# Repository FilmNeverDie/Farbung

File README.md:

# Farbung

Färbung means colouring in German, and all these effor are infact a way of colouring, thus Färbung. 
A open source project based on FilmNeverDie's CP800 film processing machine.

Project: CP800 

This project is initialized and managed by FIlmeNeverDie. Here, we introduce a rotating drum film developer. Film developing machines are getting outdated and they have run out of support, so the project aims to introduce a series of products that could replace old equipment that has no support and is hard to get replacement/maintenance services. This project provides the resources available for on-going maintenance and product support for film processing within an open-source community, so that anyone can pick up the role as a supplier and maker. We also welcome users to make their own adaptation since the need for each user might be different and the existing variation may not be ideal for each application. Please see CONTIRBUTION for how you can contribute to an existing project, or branch off to your own variant of the machine.  

## Project structure 
 
The project is separated into sections: hardware, firmware, and software 

Hardware includes a list of parts, the relevant CAD files, schematics, and respective documentation such as part lists (BOM), datasheet, user manual, maintenance manual, production manual, and certificates. 

Firmware includes the codes for programming the microcontroller, and its respective documentation such as change log, license, dependency. 

Software includes any software that enhance any parts of either the machines or film processing such as simulation, check system integrity and firmware auto-update, the processing programs generators, photo scanning and processing software and their respective documentation such as change log, license, dependency. 

Contributors will be expected writing and updating the manuals for their own variation.  

There will be a list of verified models and compatibility table that shows the combination of hardware/firmware/software compatible in the front page of each project.  

## Getting Started 

Installations 

### Firmware: 

Arduino IDE with libraries: 

- USB Host shield Library 2.0  

- DallasTemperautre + OneWire 

Get the newest stable version of source code and upload to the arduino, please check the hardware version of your machine if you purchased from FND, and download the respective firmware. 

### Hardware: 
Mechanical:
Fusion 360 
Electronics:
KiCAD5

### Software:

N/A 

## Getting Involved 

The following are areas where we are currently working on: 

Chemical tanks system: float sensors, heating 

Mechanically stronger developing tank (either stainless steel, or better printing) 

Firmware optimization to use dynamics memory less than 5kbB. 

Optional joystick modules (Arduino joystick shield), and USB/BT controller (see USB Host shield Library for the list) 

Onboard low noise low dropout voltage regulation instead of relying solely on the switching mode convertors with various quality depending on the source (see the BOM in hardware section) 

Areas that could be potential development: 

Miniature solenoid valves and poly manifolds fitting.  

Compatible microcontroller other than Arduino such as beaglebone, Rpi, Psoc, others 

Processing program generators (web base or standalone) 

A bigger and high-resolution screen, also new UI/UX, don't mind if you can fit a few “extra functions” in for bored operators to do while processing 

A computer application that searches for the newest firmware to download from GitHub for any verified hardware 

Any other suggestions 

## Documentation

This repo uses [mkdocs](https://www.mkdocs.org) to host online documentation. `mkdocs.yml` is its configuration file, and `docs/` is the directory containing the documentation pages.

## LICENSE: 

This work is licensed under a Creative Commons Attribution-ShareAlike 4.0 International License, except for source code which is licensed under the 3-Clause BSD License.

see LICENSE.md and LICENSE_CC-BY-SA.md for details

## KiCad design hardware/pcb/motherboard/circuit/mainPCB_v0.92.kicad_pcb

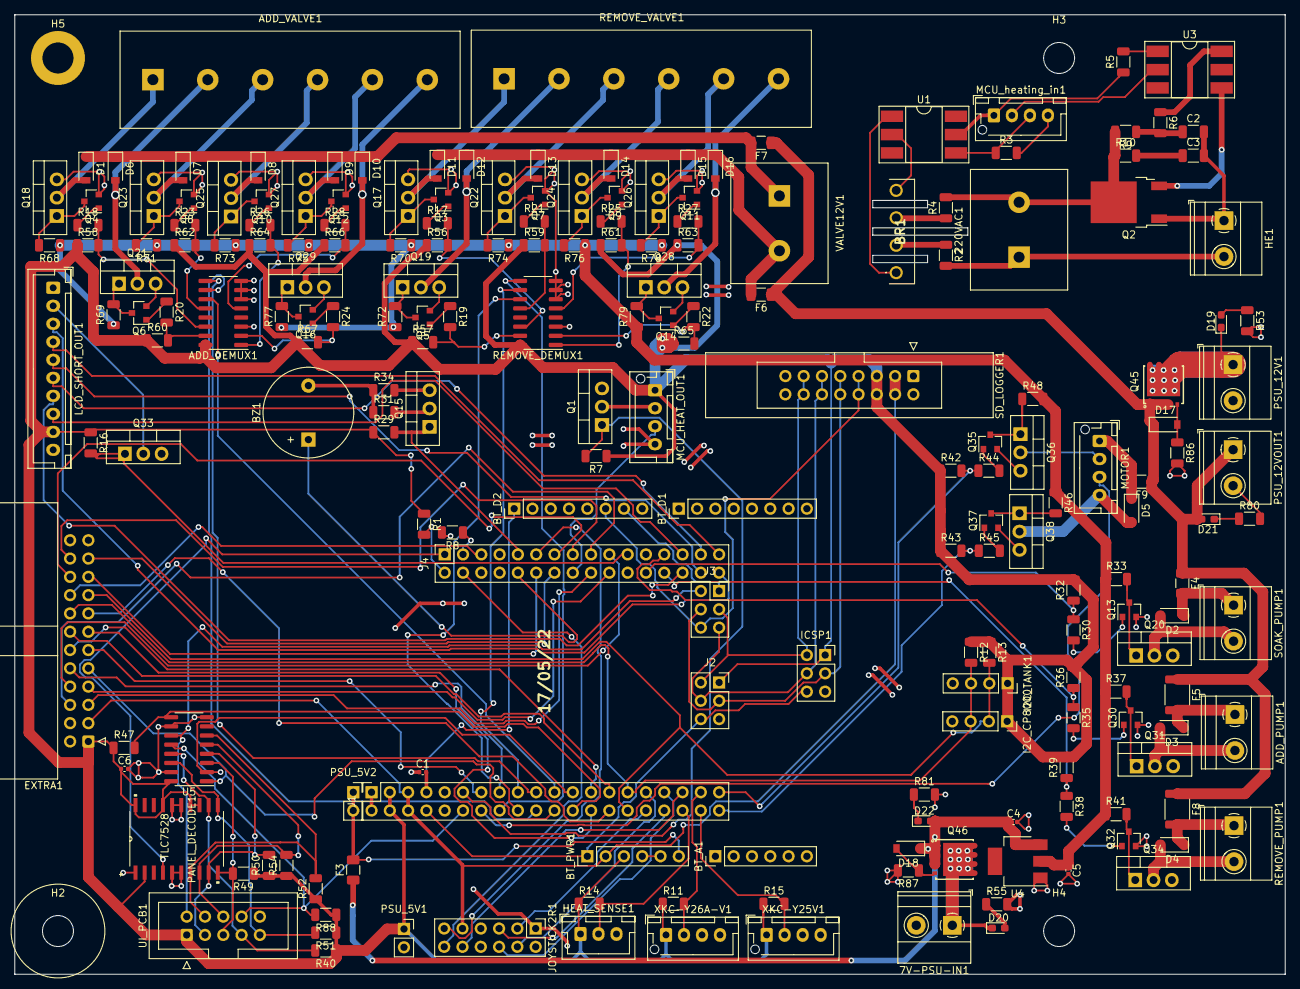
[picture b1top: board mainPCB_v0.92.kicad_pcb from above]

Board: 2 copper layers, 176.4 x 133.2 mm, 207 parts (0 on the bottom side), 174 nets.

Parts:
7V-PSU-IN1: WJ128V-5.0-2P; TerminalBlock_Phoenix_MKDS-1,5-2_1x02_P5.00mm_Horizontal
220VAC1: WJ25C-B-7.62-2P
ADD_DEMUX1: CD4051BM96; SOIC-16_3.9x9.9mm_P1.27mm
ADD_PUMP1: WJ128V-5.0-2P; TerminalBlock_Phoenix_MKDS-1,5-2_1x02_P5.00mm_Horizontal
ADD_VALVE1: WJ25C-B-7.62-6P
BR1: KBP206G
BT_A1: Conn_01x06; PinHeader_1x06_P2.54mm_Vertical
BT_D1, BT_D2: Conn_01x08; PinHeader_1x08_P2.54mm_Vertical
BT_PWR1: Conn_01x06; PinHeader_1x06_P2.54mm_Vertical
BZ1: SFN-1207PA7.6; Buzzer_12.6x7.0P7.5
C1: 100nF-ceramics; C_0402_1005Metric
C2: 47nF-ceramic; C_1206_3216Metric
C3: 10nF-ceramic; C_1206_3216Metric
C4, C5: 1.0uF; C_0402_1005Metric
C6: 0.1uF; C_0402_1005Metric
D1, D2, D3, D4, D5, D6, D7, D8, D9, D10, D11, D12, D13, D14, D15, D16: 1N5819HW-7-F; D_SOD-123
D17: MM1Z12; D_SOD-123
D18: MM1Z7V5; D_SOD-123
D19, D20: RLED; LED_0603_1608Metric_Pad1.05x0.95mm_HandSolder
D21, D22: WLED; LED_0603_1608Metric_Pad1.05x0.95mm_HandSolder
EXTRA1: 321024RG0ABK00A06; IDC-Header_2x12_P2.54mm_Horizontal
F3: BSMD1206-050-13.2V; Fuse_1206_3216Metric
F4: BSMD1206-050-16V; Fuse_1206_3216Metric
F5, F8: BSMD1812-260-13.2V; Fuse_1812_4532Metric
F6, F7: BSMD1206-100-16V; Fuse_1206_3216Metric
F9: BSMD1206-075-16V; Fuse_1206_3216Metric
H2, H3, H4: MountingHole; MountingHole_4.3mm_M4
H5: MountingHole; MountingHole_4.3mm_M4_DIN965_Pad
HE1: WJ128V-5.0-2P; TerminalBlock_Phoenix_MKDS-1,5-2_1x02_P5.00mm_Horizontal
HEAT_SENSE1: JST_XH-A-1x03; JST_XH_B3B-XH-A_1x03_P2.50mm_Vertical
I2C_CP8000, I2C_TANK1: Conn_01x04; PinSocket_1x04_P2.54mm_Vertical
ICSP1: Conn_02x03_Odd_Even; PinSocket_2x03_P2.54mm_Vertical
J1: Conn_02x20_Odd_Even; PinSocket_2x20_P2.54mm_Vertical
J2, J3: Conn_02x03_Odd_Even; PinSocket_2x03_P2.54mm_Vertical
J4: Conn_02x16_Odd_Even; PinSocket_2x16_P2.54mm_Vertical
JOYSTICK2R1: Conn_02x06_Odd_Even; PinHeader_2x06_P2.54mm_Vertical
LCD_SHORT_OUT1: JST_XH-A-1x10; JST_XH_B10B-XH-A_1x10_P2.50mm_Vertical
MCU_HEAT_OUT1: JST_XH-A-1x04; JST_XH_B4B-XH-AM_1x04_P2.50mm_Vertical
MCU_heating_in1: JST_XH-A-1x04; JST_XH_B4B-XH-AM_1x04_P2.50mm_Vertical
MOTOR1: JST_XH-A-1x04; JST_XH_B4B-XH-AM_1x04_P2.50mm_Vertical
PANEL_DECODE1: TLC7528; TLC7528CDW
PSU_5V1, PSU_5V2: Conn_01x02; PinSocket_1x02_P2.54mm_Vertical
PSU_12V1, PSU_12VOUT1: WJ128V-5.0-2P; TerminalBlock_Phoenix_MKDS-1,5-2_1x02_P5.00mm_Horizontal
Q1, Q15, Q33: IRF510PBF; TO-220-3_Vertical
Q2: BT136S-600E; TO-252-2
Q3, Q4, Q5, Q6, Q7, Q8, Q9, Q10, Q11, Q12, Q13, Q14, Q16, Q30, Q32, Q35, Q37: BC847; SOT-23
Q17, Q18, Q19, Q20, Q21, Q22, Q23, Q24, Q25, Q26, Q27, Q28, Q29, Q31, Q34, Q36, Q38: IRF540NPBF; TO-220-3_Vertical
Q45, Q46: AON6411; ALOM_DFN5X6_8L_EP1_P
R1, R7, R8, R11, R12, R13, R15, R16, R29, R30, R32, R35, R36, R38, R39, R40, R42, R43, R44, R45, R47, R49, R50, R51, R52, R54, R56, R57, R58, R59, R60, R61, R62, R63, R64, R65, R66, R67, R86, R87, R88: 10k-0.25W; R_1206_3216Metric
R2, R4: 47k-0.25W; R_1206_3216Metric
R3, R17, R18, R19, R20, R21, R22, R23, R24, R25, R26, R27, R28, R34: 1k-0.25W; R_1206_3216Metric
R5, R68, R69, R70, R71, R72, R73, R74, R75, R76, R77, R78, R79: 150-0.25W; R_1206_3216Metric
R6: 360-0.25W; R_1206_3216Metric
R9: 470-0.25W; R_1206_3216Metric
R10: 68-0.25W; R_1206_3216Metric
R14, R53, R55, R80, R81: 4.7k-0.25W; R_1206_3216Metric
R31: 220-0.25W; R_1206_3216Metric
R33, R37, R41, R46, R48: 200-0.25W; R_1206_3216Metric
REMOVE_DEMUX1: CD4051BM96; SOIC-16_3.9x9.9mm_P1.27mm
REMOVE_PUMP1: WJ128V-5.0-2P; TerminalBlock_Phoenix_MKDS-1,5-2_1x02_P5.00mm_Horizontal
REMOVE_VALVE1: WJ25C-B-7.62-6P
SD_LOGGER1: 321016SG0ABK00A01; IDC-Header_2x08_P2.54mm_Latch_Vertical
SOAK_PUMP1: WJ128V-5.0-2P; TerminalBlock_Phoenix_MKDS-1,5-2_1x02_P5.00mm_Horizontal
U1: 4N35SM; DIP-6_W8.89mm_SMDSocket_LongPads
U3: MOC3020S-TA1; DIP-6_W8.89mm_SMDSocket_LongPads
U4: AZ1117-5.0; SOT-223
U5: SN74HC165; SOIC-16_3.9x9.9mm_P1.27mm
UI_PCB1: 321010SG0ABK00A01; IDC-Header_2x05_P2.54mm_Vertical
VALVE12V1: WJ25C-B-7.62-2P
XKC-Y25V1, XKC-Y26A-V1: JST_XH-A-1x04; JST_XH_B4B-XH-AM_1x04_P2.50mm_Vertical

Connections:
5V_EX: C5.1, R33.1, R37.1, R41.1, R46.1, R48.2, R68.1, R69.1, R70.1, R71.1, R72.1, R73.1, R74.1, R75.1, R76.1, R77.1, R78.1, R79.1, U4.2
220VAC+: 220VAC1.2, Q2.2, R4.2, R9.2, R10.1
220VAC-: 220VAC1.1, HE1.2, R2.2
+3V3: BT_PWR1.2, EXTRA1.3, J1.5, J1.6, JOYSTICK2R1.9, SD_LOGGER1.3, SD_LOGGER1.4
+5V: ADD_DEMUX1.16, BT_PWR1.3, C6.1, EXTRA1.1, HEAT_SENSE1.1, I2C_CP8000.1, I2C_TANK1.1, ICSP1.1, J1.3, J1.4, J2.1, LCD_SHORT_OUT1.9, MCU_HEAT_OUT1.1, PANEL_DECODE1.2, PANEL_DECODE1.13, PANEL_DECODE1.14, PANEL_DECODE1.17, PANEL_DECODE1.20, PSU_5V1.1, R1.1, R7.1, R11.1, R12.1, R13.1, R14.1, R15.1, R16.1, R29.1, R32.2, R36.2, R39.2, R40.1, R42.1, R43.1, R47.1, R49.1, R50.1, R51.1, R52.1, R54.1, R56.1, R57.1, R58.1, R59.1, R60.1, R61.1, R62.1, R63.1, R64.1, R65.1, R66.1, R67.1, R88.1, REMOVE_DEMUX1.16, SD_LOGGER1.5, SD_LOGGER1.6, U5.16, UI_PCB1.1, XKC-Y25V1.1, XKC-Y26A-V1.1
+12V: D17.1, D21.2, F4.1, F5.1, F6.1, F7.1, F8.1, F9.1, PSU_12VOUT1.1, Q45.1, Q45.2, Q45.3
/5V+in: MCU_heating_in1.1, R5.1, U1.5
/Aref: BT_D2.1, C1.2, J1.7
/Dpad_down: PANEL_DECODE1.11, R51.2, U5.14, UI_PCB1.9
/Dpad_left: PANEL_DECODE1.10, R49.2, U5.3, UI_PCB1.5
/Dpad_right: PANEL_DECODE1.12, R40.2, U5.13, UI_PCB1.7
/Dpad_up: PANEL_DECODE1.9, R50.2, U5.4, UI_PCB1.3
/cancel: PANEL_DECODE1.8, R54.2, U5.5, UI_PCB1.6
/heat_PWMo: MCU_HEAT_OUT1.2, Q1.2
/heat_control: C2.2, C3.2, HE1.1, Q2.1
/reset: BT_PWR1.1, ICSP1.6, J1.8, J2.6
/select: PANEL_DECODE1.7, R52.2, U5.6, UI_PCB1.4
A0: J4.1, PANEL_DECODE1.4
A1: J4.2, R1.2
A2: J4.3, R8.1
A3: J4.4, JOYSTICK2R1.12
A4: EXTRA1.18, J4.5
A8: J4.9, Q15.1, R29.2
A9: BZ1.1, J4.10
A10: J4.11, JOYSTICK2R1.11
A11: EXTRA1.19, J4.12
A12: EXTRA1.20, J4.13
A13: EXTRA1.21, J4.14
A14: EXTRA1.22, J4.15
A15: J4.16, MCU_HEAT_OUT1.3
D2: J1.11, Q1.1, R7.2
D3: J1.12, R88.2, U5.12, UI_PCB1.8
D4: EXTRA1.11, J1.13
D5: J1.14, MOTOR1.3
D6: EXTRA1.10, J1.15
D7: J1.16, REMOVE_DEMUX1.9
D8: J1.17, REMOVE_DEMUX1.10
D9: J1.18, REMOVE_DEMUX1.11
D10: ADD_DEMUX1.9, J1.19
D11: ADD_DEMUX1.10, J1.20
D12: ADD_DEMUX1.11, J1.21
D13: EXTRA1.9, J1.22, U5.1
D14: J1.23, U5.2
D15: J1.24, R47.2, U5.9
D16: EXTRA1.12, J1.25
D17: EXTRA1.13, J1.26
D18: EXTRA1.14, J1.27
D19: EXTRA1.15, J1.28
D20: EXTRA1.16, I2C_CP8000.3, I2C_TANK1.3, J1.29, R12.2
D21: EXTRA1.17, I2C_CP8000.2, I2C_TANK1.2, J1.30, R13.2
D22: J1.31, JOYSTICK2R1.4
D23: J1.32, JOYSTICK2R1.3
D24: J1.33, JOYSTICK2R1.6
D25: J1.34, JOYSTICK2R1.5
D26: J1.35, JOYSTICK2R1.10
D27: HEAT_SENSE1.2, J1.36, R14.2
D28: J1.37, R11.2, XKC-Y26A-V1.2
D29: J1.38, R15.2, XKC-Y25V1.2
D30: J1.39, R42.2, R44.1
D31: J1.40, R43.2, R45.1
D32: EXTRA1.6, J4.17
D33: EXTRA1.5, J4.18
D34: EXTRA1.8, J4.19
D35: EXTRA1.7, J4.20
D36: J4.21, Q33.1, R16.2
D39: J4.24, R30.1, R32.1
D40: J4.25, R35.1, R36.1
D41: J4.26, R38.1, R39.1
D42: J4.27, LCD_SHORT_OUT1.8
D43: J4.28, LCD_SHORT_OUT1.7
D44: J4.29, LCD_SHORT_OUT1.6
D45: J4.30, LCD_SHORT_OUT1.5
D46: J4.31, LCD_SHORT_OUT1.4
D47: J4.32, LCD_SHORT_OUT1.3
D48: BT_D2.7, J3.1
D49: J3.2, U5.11, UI_PCB1.2
D50: ICSP1.2, J2.2, J3.3, SD_LOGGER1.13, SD_LOGGER1.14
D51: ICSP1.3, J2.3, J3.4, SD_LOGGER1.9, SD_LOGGER1.10
D52: ICSP1.4, J2.4, J3.5, SD_LOGGER1.11, SD_LOGGER1.12
D53: BT_D2.6, J3.6, SD_LOGGER1.7, SD_LOGGER1.8
unnamed: ADD_DEMUX1.1, R26.2, R64.2
unnamed: ADD_DEMUX1.2, R24.2, R67.2
unnamed: ADD_DEMUX1.5, R28.2, R66.2
unnamed: ADD_DEMUX1.12, R23.2, R62.2
unnamed: ADD_DEMUX1.14, R18.2, R58.2
unnamed: ADD_DEMUX1.15, R20.2, R60.2
unnamed: ADD_PUMP1.1, D3.1, F5.2
unnamed: ADD_PUMP1.2, D3.2, Q31.2
unnamed: ADD_VALVE1.1, D1.2, Q18.2
unnamed: ADD_VALVE1.2, D6.2, Q21.2
unnamed: ADD_VALVE1.3, D7.2, Q23.2
unnamed: ADD_VALVE1.4, D8.2, Q25.2
unnamed: ADD_VALVE1.5, D9.2, Q27.2
unnamed: ADD_VALVE1.6, D10.2, Q29.2
unnamed: BR1.1, U1.1
unnamed: BR1.2, R2.1
unnamed: BR1.3, R4.1
unnamed: BR1.4, U1.2
unnamed: BZ1.2, R31.1, R34.1
unnamed: C2.1, R6.2, R9.1
unnamed: C3.1, R10.2
unnamed: D1.1, D6.1, D7.1, D8.1, D9.1, D10.1, F7.2, VALVE12V1.1
unnamed: D2.1, F4.2, SOAK_PUMP1.1
unnamed: D2.2, Q20.2, SOAK_PUMP1.2
unnamed: D4.1, F8.2, REMOVE_PUMP1.1
unnamed: D4.2, Q34.2, REMOVE_PUMP1.2
unnamed: D5.1, F9.2, MOTOR1.1
unnamed: D5.2, MOTOR1.4, Q38.2
unnamed: D11.1, D12.1, D13.1, D14.1, D15.1, D16.1, F6.2, VALVE12V1.2
unnamed: D11.2, Q17.2, REMOVE_VALVE1.1
unnamed: D12.2, Q19.2, REMOVE_VALVE1.2
unnamed: D13.2, Q22.2, REMOVE_VALVE1.3
unnamed: D14.2, Q24.2, REMOVE_VALVE1.4
unnamed: D15.2, Q26.2, REMOVE_VALVE1.5
unnamed: D16.2, Q28.2, REMOVE_VALVE1.6
unnamed: D17.2, Q45.4, R86.1
unnamed: D18.2, Q46.4, R87.1
unnamed: D19.2, R53.1
unnamed: D20.2, R55.1
unnamed: D21.1, R80.1
unnamed: D22.1, R81.1
unnamed: LCD_SHORT_OUT1.2, Q33.2
unnamed: MCU_heating_in1.2, U3.2
unnamed: MCU_heating_in1.3, R3.1, U1.4
unnamed: MOTOR1.2, Q36.2
unnamed: Q2.3, U3.4
unnamed: Q3.1, R17.1
unnamed: Q4.1, R18.1
unnamed: Q5.1, R19.1
unnamed: Q6.1, R20.1
unnamed: Q7.1, R21.1
unnamed: Q8.1, R23.1
unnamed: Q9.1, R25.1
unnamed: Q10.1, R26.1
unnamed: Q10.3, Q25.1, R73.2
unnamed: Q11.1, R27.1
unnamed: Q11.3, Q26.1, R78.2
unnamed: Q12.1, R28.1
unnamed: Q12.3, Q27.1, R75.2
unnamed: Q13.1, R30.2
unnamed: Q13.3, Q20.1, R33.2
unnamed: Q14.1, R22.1
unnamed: Q14.3, Q28.1, R79.2
unnamed: Q15.2, R31.2
unnamed: Q16.1, R24.1
unnamed: Q16.3, Q29.1, R77.2
unnamed: Q3.3, Q17.1, R70.2
unnamed: Q4.3, Q18.1, R68.2
unnamed: Q5.3, Q19.1, R72.2
unnamed: Q6.3, Q21.1, R69.2
unnamed: Q7.3, Q22.1, R74.2
unnamed: Q8.3, Q23.1, R71.2
unnamed: Q9.3, Q24.1, R76.2
unnamed: Q30.1, R35.2
unnamed: Q30.3, Q31.1, R37.2
unnamed: Q32.1, R38.2
unnamed: Q32.3, Q34.1, R41.2
unnamed: Q35.1, R44.2
unnamed: Q35.3, Q36.1, R48.1
unnamed: Q37.1, R45.2
unnamed: Q37.3, Q38.1, R46.2
unnamed: R5.2, U3.1
unnamed: R6.1, U3.6
unnamed: R17.2, R56.2, REMOVE_DEMUX1.14
unnamed: R19.2, R57.2, REMOVE_DEMUX1.15
unnamed: R21.2, R59.2, REMOVE_DEMUX1.12
unnamed: R22.2, R65.2, REMOVE_DEMUX1.2
unnamed: R25.2, R61.2, REMOVE_DEMUX1.1
unnamed: R27.2, R63.2, REMOVE_DEMUX1.5
PSU_12V+: D19.1, PSU_12V1.1, Q45.5, Q45.6, Q45.7, Q45.8, Q45.9
PSU_12VGND: 7V-PSU-IN1.2, ADD_DEMUX1.3, ADD_DEMUX1.6, ADD_DEMUX1.7, ADD_DEMUX1.8, BT_D2.2, BT_PWR1.4, BT_PWR1.5, C1.1, C4.2, C5.2, C6.2, EXTRA1.23, EXTRA1.24, HEAT_SENSE1.3, I2C_CP8000.4, I2C_TANK1.4, ICSP1.5, J1.1, J1.2, J2.5, JOYSTICK2R1.1, LCD_SHORT_OUT1.1, LCD_SHORT_OUT1.10, MCU_HEAT_OUT1.4, MCU_heating_in1.4, PANEL_DECODE1.1, PANEL_DECODE1.5, PANEL_DECODE1.6, PANEL_DECODE1.15, PANEL_DECODE1.16, PSU_5V1.2, PSU_12V1.2, PSU_12VOUT1.2, Q1.3, Q3.2, Q4.2, Q5.2, Q6.2, Q7.2, Q8.2, Q9.2, Q10.2, Q11.2, Q12.2, Q13.2, Q14.2, Q15.3, Q16.2, Q17.3, Q18.3, Q19.3, Q20.3, Q21.3, Q22.3, Q23.3, Q24.3, Q25.3, Q26.3, Q27.3, Q28.3, Q29.3, Q30.2, Q31.3, Q32.2, Q33.3, Q34.3, Q35.2, Q36.3, Q37.2, Q38.3, R3.2, R8.2, R34.2, R53.2, R55.2, R80.2, R81.2, R86.2, R87.2, REMOVE_DEMUX1.3, REMOVE_DEMUX1.6, REMOVE_DEMUX1.7, REMOVE_DEMUX1.8, SD_LOGGER1.15, SD_LOGGER1.16, U4.1, U5.8, U5.10, U5.15, UI_PCB1.10, XKC-Y25V1.3, XKC-Y25V1.4, XKC-Y26A-V1.3, XKC-Y26A-V1.4
PSU_V+: C4.1, D18.1, D22.2, F3.1, Q46.1, Q46.2, Q46.3, U4.3
PSU_VIN: 7V-PSU-IN1.1, D20.1, Q46.5, Q46.6, Q46.7, Q46.8, Q46.9
Vin: BT_PWR1.6, F3.2, PSU_5V2.1, PSU_5V2.2

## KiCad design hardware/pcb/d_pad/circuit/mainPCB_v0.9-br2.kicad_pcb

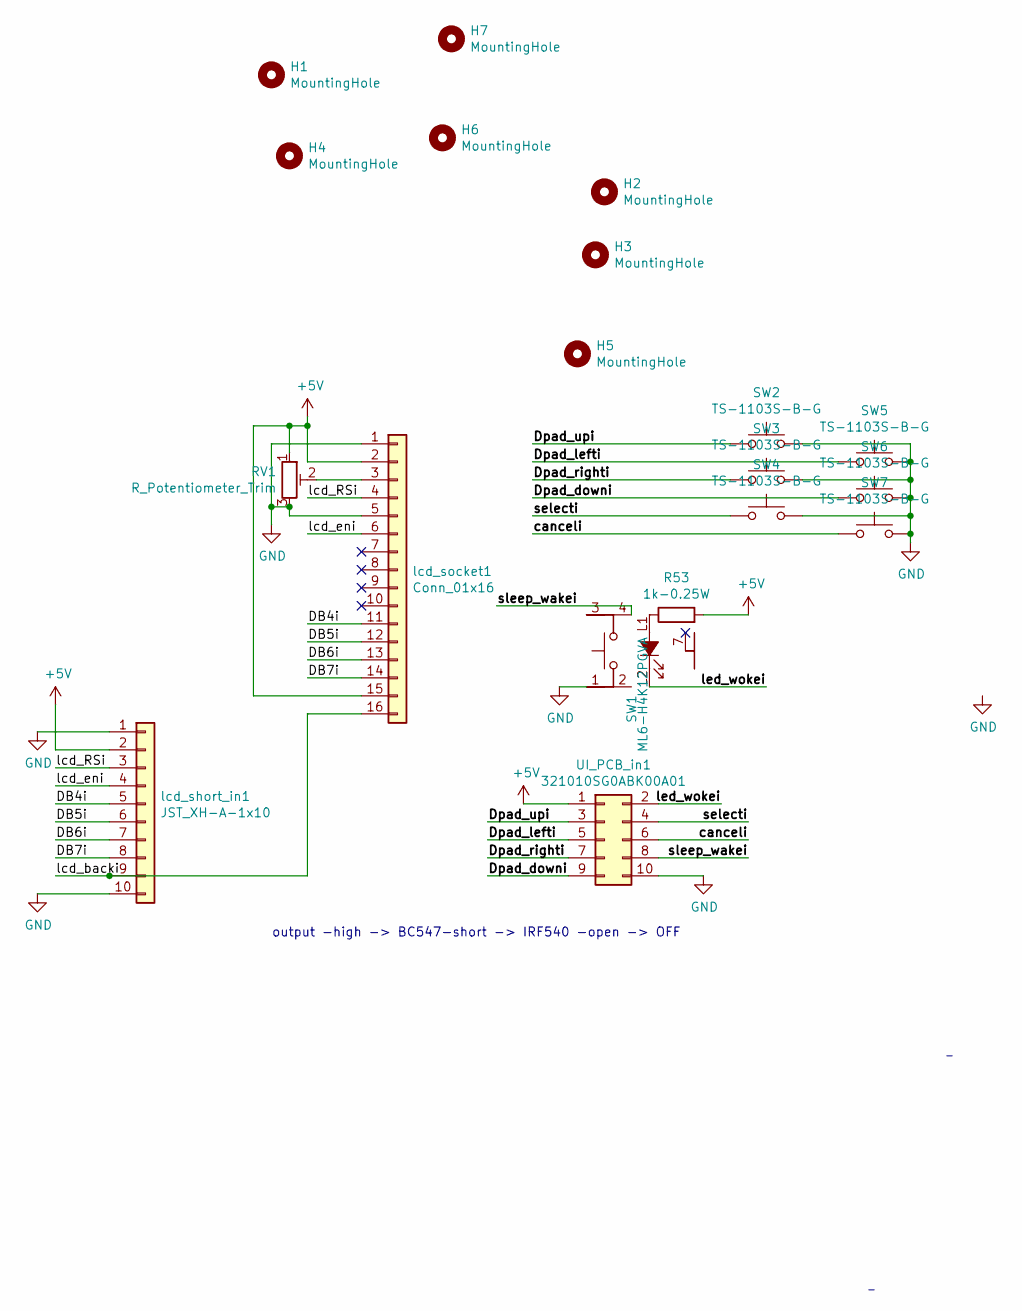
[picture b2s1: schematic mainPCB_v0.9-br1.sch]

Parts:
H1, H2, H3, H4, H6, H7: MountingHole; MountingHole_3.2mm_M3
H5: MountingHole; MountingHole_4.5mm
R53: 1k-0.25W; R_1206_3216Metric; LCSC C4410
RV1: R_Potentiometer_Trim; VG039NCHXTB102; LCSC C128543
SW1: ML6-H4K12PGVA; ML6-H4; LCSC C225014
SW2, SW3, SW4, SW5, SW6, SW7: TS-1103S-B-G; TS-1103S-X-X; LCSC C480306
UI_PCB_in1: 321010SG0ABK00A01; IDC-Header_2x05_P2.54mm_Vertical; LCSC C49661
lcd_short_in1: JST_XH-A-1x10; JST_XH_B10B-XH-A_1x10_P2.50mm_Vertical; LCSC C144400
lcd_socket1: Conn_01x16; PinHeader_1x16_P2.54mm_Vertical; LCSC C49661

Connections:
+5V: R53.2, RV1.1, UI_PCB_in1.1, lcd_short_in1.2, lcd_socket1.2, lcd_socket1.15
/DB4i: lcd_short_in1.5, lcd_socket1.11
/DB5i: lcd_short_in1.6, lcd_socket1.12
/DB6i: lcd_short_in1.7, lcd_socket1.13
/DB7i: lcd_short_in1.8, lcd_socket1.14
/Dpad_downi: SW6.1, UI_PCB_in1.9
/Dpad_lefti: SW5.1, UI_PCB_in1.5
/Dpad_righti: SW3.1, UI_PCB_in1.7
/Dpad_upi: SW2.1, UI_PCB_in1.3
/canceli: SW7.1, UI_PCB_in1.6
/lcd_RSi: lcd_short_in1.3, lcd_socket1.4
/lcd_backi: lcd_short_in1.9, lcd_socket1.16
/lcd_eni: lcd_short_in1.4, lcd_socket1.6
/led_wokei: SW1.L2 (K), UI_PCB_in1.2
/selecti: SW4.1, UI_PCB_in1.4
/sleep_wakei: SW1.4, UI_PCB_in1.8
GND: RV1.3, SW1.1, SW2.2, SW3.2, SW4.2, SW5.2, SW6.2, SW7.2, UI_PCB_in1.10, lcd_short_in1.1, lcd_short_in1.10, lcd_socket1.1, lcd_socket1.5
unnamed: R53.1, SW1.L1 (A)
unnamed: RV1.2, lcd_socket1.3

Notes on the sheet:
output -high -> BC547-short -> IRF540 -open -> OFF

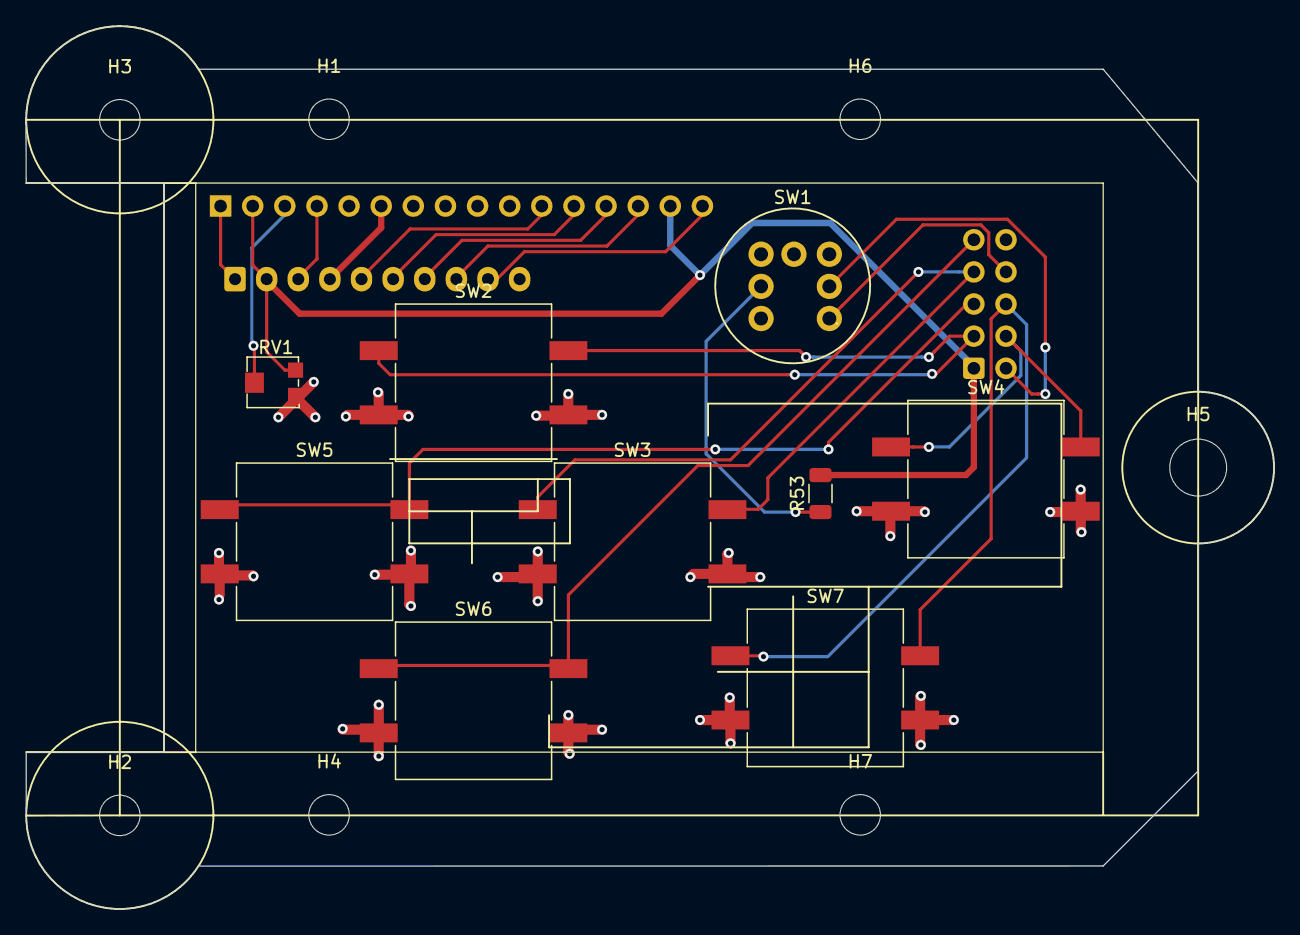
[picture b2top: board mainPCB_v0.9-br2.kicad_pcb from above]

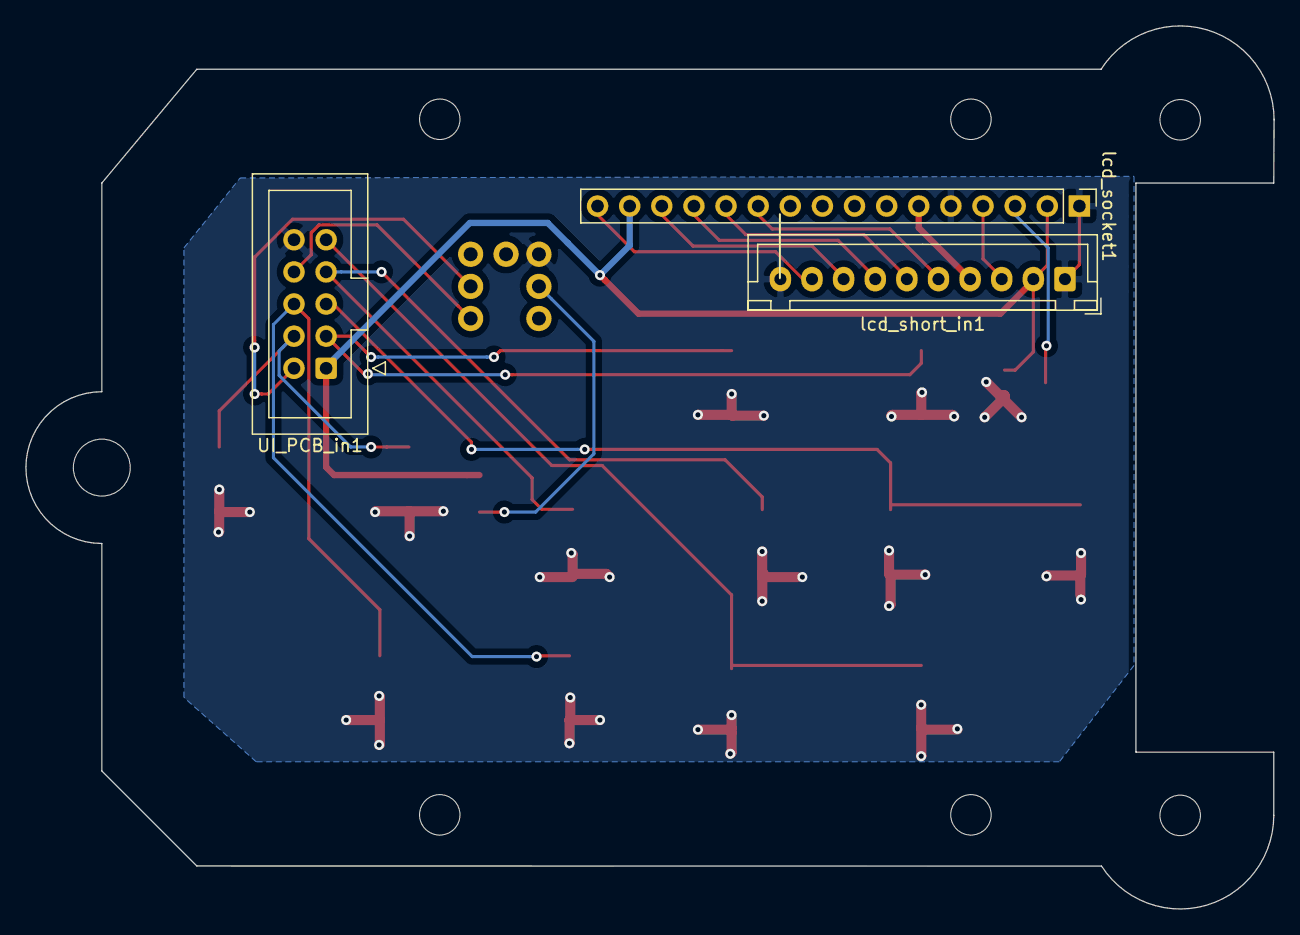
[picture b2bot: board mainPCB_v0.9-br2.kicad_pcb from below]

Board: 2 copper layers, 98.7 x 69.8 mm, 19 parts (3 on the bottom side), 19 nets.

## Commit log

2022-04-20 Create LICENSE
2022-04-20 Update LICENSE
2022-04-25 Create CONTRIBUTING.md
    still missing optimsation contribution, and document need review
2022-07-16 Create CP800 Assembly document, videos and Inventory list
2022-10-22 Delete usermanual (1).docx
    New and updated version to come
2022-10-28 Create CP800 3D files
2022-10-28 Create CP800 PCBs
2022-10-28 Create CP800 arduino program
2022-10-28 Update CP800 arduino program
2022-10-28 Update CP800 3D files
2022-12-18 Convert "CP800 - software.docx" to markdown
2022-12-18 Convert "CP800 issues and roadmap" to md
2022-12-19 Multiple changes, see description
    Added firmware and software files from sharepoint
    Set up mkdocs documentation
    Converted .docx files to .md
    Licensed source code under 3-clause BSD
2022-12-19 Add welcome message to wiki
2022-12-19 Create automated documentation deployment
2022-12-19 Run docs deployment only when 'docs/' modified
2022-12-19 Revert docs to ReadTheDocs theme
2022-12-19 Add motherboard hardware files
2022-12-19 Change docs site URL to use FilmNeverDie.github.io
2022-12-19 Build mkdocs site when config changes
2023-01-01 Update ROADMAP.md
    remove irrelevant item on the future project list
2023-01-01 Install mkdocs during pages deploy action
2023-01-01 Add workflow_dispatch trigger to action
2023-01-17 Deployed 537c44a with MkDocs version: 1.4.2

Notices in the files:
parts and their libraries:
Copyright 2021 Accelerated Designs. All rights reserved.
